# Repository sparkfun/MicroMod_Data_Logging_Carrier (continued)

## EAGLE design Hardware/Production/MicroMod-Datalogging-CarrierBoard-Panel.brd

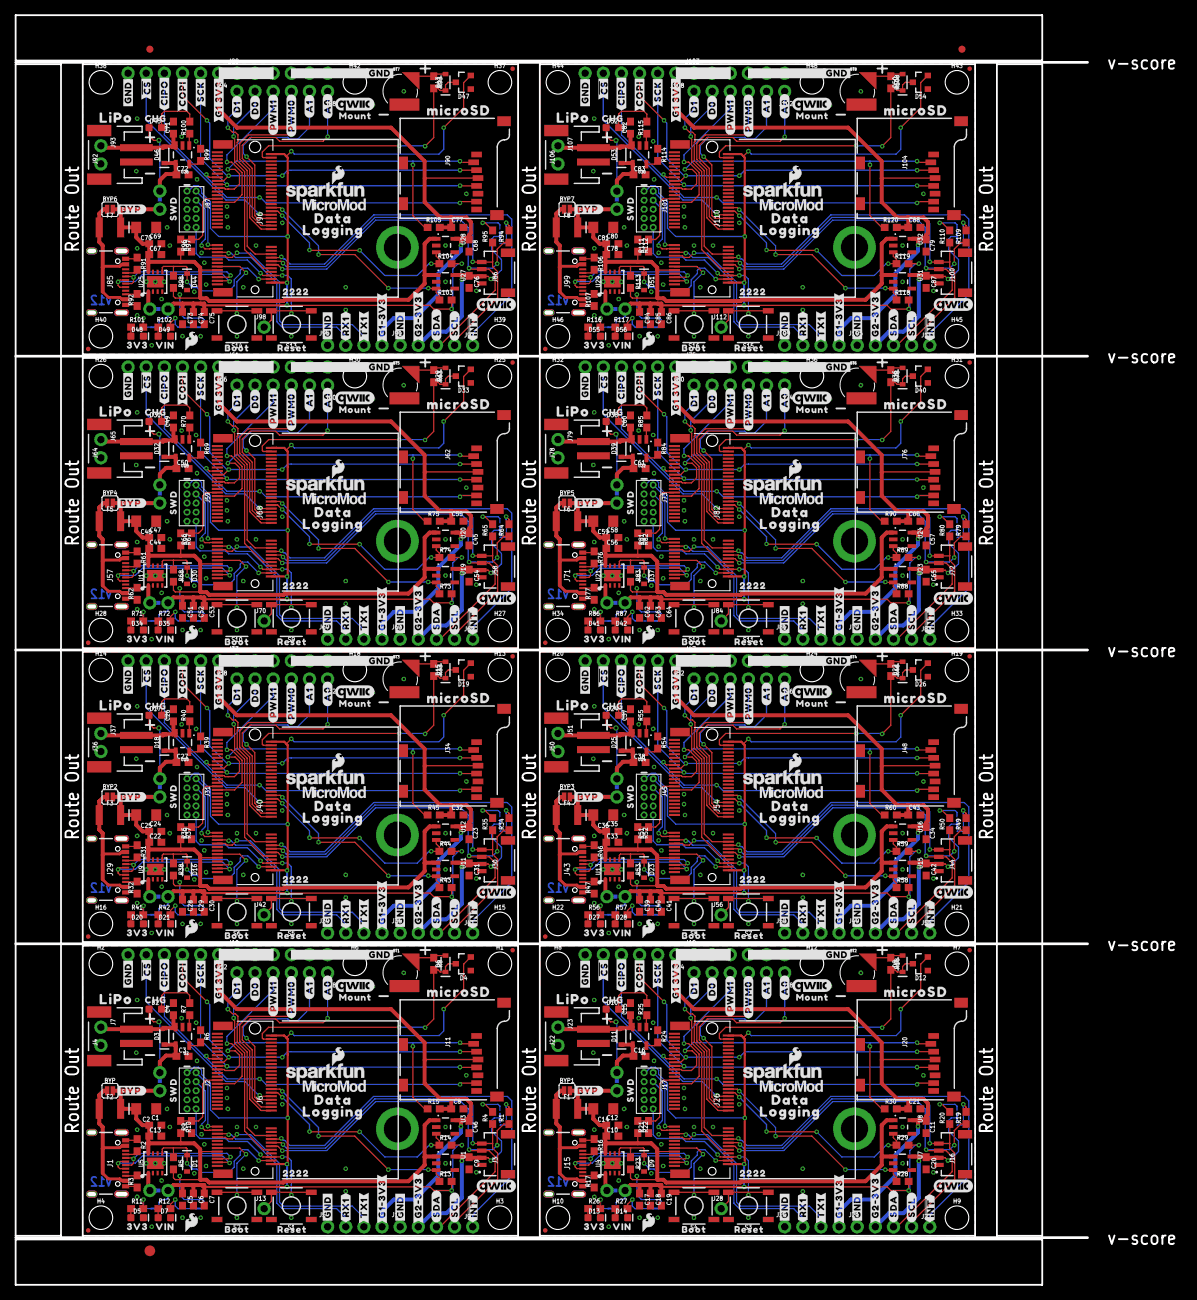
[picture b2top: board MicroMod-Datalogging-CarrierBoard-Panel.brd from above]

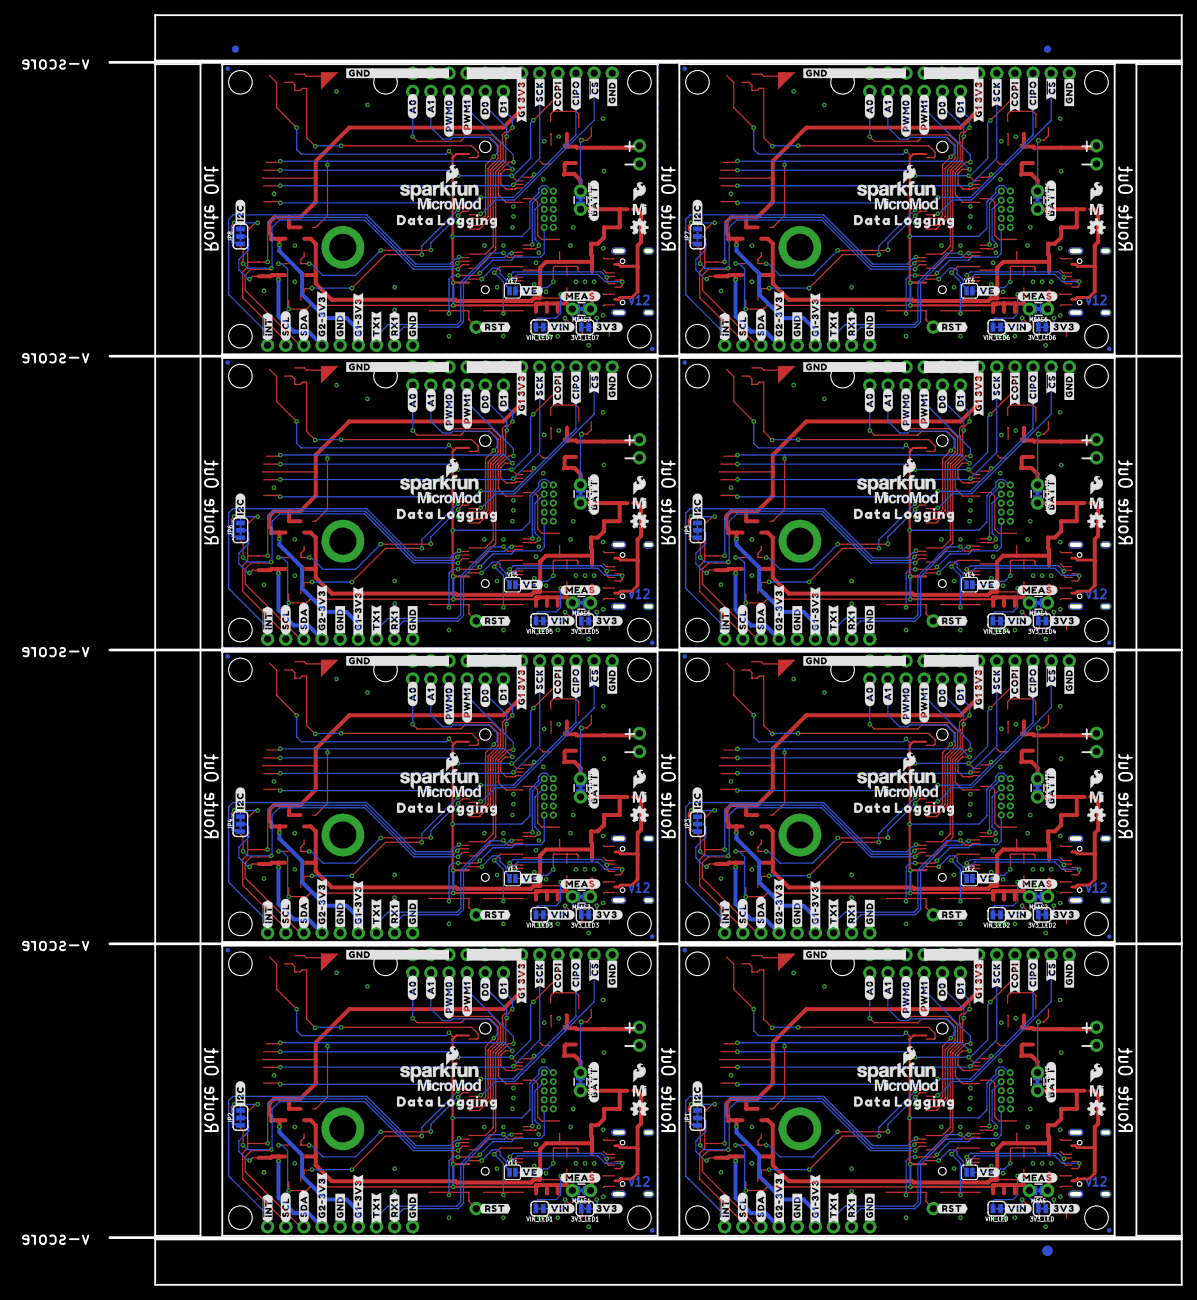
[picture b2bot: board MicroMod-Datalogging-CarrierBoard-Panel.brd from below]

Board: 2 copper layers, 163.1 x 177.5 mm, 1190 parts (355 on the bottom side), 392 nets.

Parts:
3V3_LED, 3V3_LED1, 3V3_LED2, 3V3_LED3, 3V3_LED4, 3V3_LED5, 3V3_LED6, 3V3_LED7: SMT-JUMPER_2_NC_TRACE_SILK
BT1, BT2, BT3, BT4, BT5, BT6, BT7, BT8: ML414H; ML414H_IV01E
BYP, BYP1, BYP2, BYP3, BYP4, BYP5, BYP6, BYP7: JUMPER-SMT_2_NO_SILK; SMT-JUMPER_2_NO_SILK
C1, C6, C11, C12, C18, C23, C24, C29, C34, C35, C40, C45, C46, C47, C52, C57, C58, C63, C68, C69, C74, C79, C80, C85: 0.1uF; 0603
C2, C14, C25, C36, C48, C59, C70, C81: 10uF; EIA3216
C3, C4, C15, C16, C26, C27, C37, C38, C49, C50, C60, C61, C71, C72, C82, C83: 4.7uF; 0603
C5, C8, C9, C17, C20, C21, C28, C31, C32, C39, C42, C43, C51, C54, C55, C62, C65, C66, C73, C76, C77, C84, C87, C88: 1.0uF; 0603
C7, C10, C13, C19, C22, C30, C33, C41, C44, C53, C56, C64, C67, C75, C78, C86: 0.22uF; 0603
D1, D9, D16, D23, D30, D37, D44, D51: 3.3V; SOD-323
D2, D7, D10, D14, D17, D21, D24, D28, D31, D35, D38, D42, D45, D49, D52, D56: Yellow; LED-0603
D3, D6, D8, D11, D15, D18, D22, D25, D29, D32, D36, D39, D43, D46, D50, D53: 3A/10V/280mV; SOD-323
D4, D12, D19, D26, D33, D40, D47, D54: BAS70-05; SOT23-3
D5, D13, D20, D27, D34, D41, D48, D55: RED; LED-0603
E$1, E$2, E$3, E$4: FIDUCIAL-1X2
E$5, E$6: FIDUCIAL-1.5X3
F1, F2, F3, F4, F5, F6, F7, F8: 6V/2A; 1210
FD1, FD2, FD3, FD4, FD5, FD6, FD7, FD8, FD9, FD10, FD11, FD12, FD13, FD14, FD15, FD16, FD17, FD18, FD19, FD20, FD21, FD22, FD23, FD24, FD25, FD26, FD27, FD28, FD29, FD30, FD31, FD32: FIDUCIALUFIDUCIAL; FIDUCIAL-MICRO
H1, H2, H3, H4, H6, H7, H8, H9, H10, H12, H13, H14, H15, H16, H18, H19, H20, H21, H22, H24, H25, H26, H27, H28, H30, H31, H32, H33, H34, H36, H37, H38, H39, H40, H42, H43, H44, H45, H46, H48: STAND-OFF
H5, H11, H17, H23, H29, H35, H41, H47: STAND-OFF-REFLOW2.5MM_TALL; STAND-OFF-REFLOW-M2.5
J1, J15, J29, J43, J57, J71, J85, J99: USB-C-16P-2LAYER-PADS
J2, J17, J31, J45, J59, J73, J87, J101: JTAG; 2X5-PTH-1.27MM
J3, J16, J30, J44, J58, J72, J86, J100: QWIIC_RIGHT_ANGLE; JST04_1MM_RA
J4, J22, J36, J50, J64, J78, J92, J106: JST-2-SMD
J5, J25, J39, J53, J67, J81, J95, J109: UART; 1X04_NO_SILK
J6, J26, J40, J54, J68, J82, J96, J110: MICROMOD-2222-C; M.2-CONNECTOR-E
J7, J23, J37, J51, J65, J79, J93, J107: 1X02_NO_SILK
J8, J18, J32, J46, J60, J74, J88, J102: Dedicated; 1X06_NO_SILK
J9, J13, J27, J28, J41, J42, J55, J56, J69, J70, J83, J84, J97, J98, J111, J112: 1X01_NO_SILK
J10, J19, J33, J47, J61, J75, J89, J103: 1X06_NO_SILK
J11, J20, J34, J48, J62, J76, J90, J104: microSD; MICRO-SD-SOCKET
J12, J24, J38, J52, J66, J80, J94, J108: SPI; 1X06_NO_SILK
J14, J21, J35, J49, J63, J77, J91, J105: I2C; 1X04_NO_SILK
JP1, JP2, JP3, JP4, JP5, JP6, JP7, JP8: SMT-JUMPER_3_2-NC_TRACE_SILK
LOGO1, LOGO4, LOGO6, LOGO9, LOGO11, LOGO14, LOGO16, LOGO19, LOGO21, LOGO24, LOGO26, LOGO29, LOGO31, LOGO34, LOGO36, LOGO39: SFE_LOGO_NAME_FLAME.1_INCH; SFE_LOGO_NAME_FLAME_.1
LOGO2, LOGO5, LOGO7, LOGO10, LOGO12, LOGO15, LOGO17, LOGO20, LOGO22, LOGO25, LOGO27, LOGO30, LOGO32, LOGO35, LOGO37, LOGO40: QWIIC_LOGO_CONNECTOR; QWIIC_5.5MM
LOGO3, LOGO8, LOGO13, LOGO18, LOGO23, LOGO28, LOGO33, LOGO38: OSHW-LOGOMINI; OSHW-LOGO-MINI
MEAS, MEAS1, MEAS2, MEAS3, MEAS4, MEAS5, MEAS6, MEAS7: COMBO-JUMPER_2_NC_TRACE
MEAS_BATT, MEAS_BATT1, MEAS_BATT2, MEAS_BATT3, MEAS_BATT4, MEAS_BATT5, MEAS_BATT6, MEAS_BATT7: COMBO-JUMPER_2_NC_TRACE
R1, R4, R6, R19, R20, R24, R34, R35, R39, R49, R50, R54, R64, R65, R69, R79, R80, R84, R94, R95, R99, R109, R110, R114: 2.2k; 0603
R2, R3, R16, R17, R31, R32, R46, R47, R61, R62, R76, R77, R91, R92, R106, R107: 5.1k; 0603
R5, R13, R14, R15, R23, R28, R29, R30, R38, R43, R44, R45, R53, R58, R59, R60, R68, R73, R74, R75, R83, R88, R89, R90, R98, R103, R104, R105, R113, R118, R119, R120: 100k; 0603
R7, R11, R25, R26, R40, R41, R55, R56, R70, R71, R85, R86, R100, R101, R115, R116: 1k; 0603
R8, R18, R33, R48, R63, R78, R93, R108: 3.3k; 0603
R9, R21, R36, R51, R66, R81, R96, R111: 10k; 0603
R10, R22, R37, R52, R67, R82, R97, R112: 20k; 0603
R12, R27, R42, R57, R72, R87, R102, R117: 4.7k; 0603
S1, S3, S5, S7, S9, S11, S13, S15: Reset; TACTILE_SWITCH_SMD_5.2MM
S2, S4, S6, S8, S10, S12, S14, S16: BOOT; TACTILE_SWITCH_SMD_5.2MM
U1, U3, U7, U8, U11, U12, U15, U16, U19, U20, U23, U24, U27, U28, U31, U32: 3.3V; SOT23-5
U2, U6, U10, U14, U18, U22, U26, U30: MCP73831; SOT23-5
U4, U5, U9, U13, U17, U21, U25, U29: AP7361C-33; UDFN-8
U$1, U$45, U$47, U$66, U$145, U$147, U$216, U$218, U$287, U$289, U$358, U$360, U$429, U$431, U$500, U$502: SFE_LOGO_FLAME_.1
U$2, U$58, U$76, U$118, U$156, U$189, U$227, U$260, U$298, U$331, U$369, U$402, U$440, U$473, U$511, U$544: #D1#0
U$3, U$59, U$77, U$119, U$157, U$190, U$228, U$261, U$299, U$332, U$370, U$403, U$441, U$474, U$512, U$545: #D0#0
U$4, U$133, U$204, U$275, U$346, U$417, U$488, U$559: #3V3#2
U$5, U$137, U$208, U$279, U$350, U$421, U$492, U$563: #BATT#0
U$6, U$18, U$24, U$27, U$32, U$34, U$36, U$42, U$105, U$106, U$107, U$108, U$109, U$110, U$138, U$142, U$176, U$177, U$178, U$179, U$180, U$181, U$209, U$213, U$247, U$248, U$249, U$250, U$251, U$252, U$280, U$284, U$318, U$319, U$320, U$321, U$322, U$323, U$351, U$355, U$389, U$390, U$391, U$392, U$393, U$394, U$422, U$426, U$460, U$461, U$462, U$463, U$464, U$465, U$493, U$497, U$531, U$532, U$533, U$534, U$535, U$536, U$564, U$568: #GND#0
U$7, U$8, U$52, U$53, U$150, U$151, U$221, U$222, U$292, U$293, U$363, U$364, U$434, U$435, U$505, U$506: #SCK#0
U$9, U$68, U$81, U$120, U$161, U$191, U$232, U$262, U$303, U$333, U$374, U$404, U$445, U$475, U$516, U$546: #PWM1#1
U$10, U$67, U$80, U$121, U$160, U$192, U$231, U$263, U$302, U$334, U$373, U$405, U$444, U$476, U$515, U$547: #PWM0#0
U$11, U$125, U$196, U$267, U$338, U$409, U$480, U$551: MICROSD0
U$12, U$61, U$79, U$122, U$159, U$193, U$230, U$264, U$301, U$335, U$372, U$406, U$443, U$477, U$514, U$548: #A1#2
U$13, U$60, U$78, U$123, U$158, U$194, U$229, U$265, U$300, U$336, U$371, U$407, U$442, U$478, U$513, U$549: #A0#3
U$14, U$124, U$195, U$266, U$337, U$408, U$479, U$550: MOUNT0
U$15, U$126, U$197, U$268, U$339, U$410, U$481, U$552: LIPO0
U$16, U$23, U$127, U$130, U$198, U$201, U$269, U$272, U$340, U$343, U$411, U$414, U$482, U$485, U$553, U$556: DATA0
U$17, U$71, U$86, U$111, U$164, U$182, U$235, U$253, U$306, U$324, U$377, U$395, U$448, U$466, U$519, U$537: #RX1#1
U$19, U$26, U$128, U$131, U$199, U$202, U$270, U$273, U$341, U$344, U$412, U$415, U$483, U$486, U$554, U$557: LOGGING1
U$20, U$129, U$200, U$271, U$342, U$413, U$484, U$555: 22220
U$21, U$84, U$89, U$112, U$167, U$183, U$238, U$254, U$309, U$325, U$380, U$396, U$451, U$467, U$522, U$538: #TX1#2
U$22, U$132, U$203, U$274, U$345, U$416, U$487, U$558: #I2C#0
U$25, U$85, U$90, U$113, U$168, U$184, U$239, U$255, U$310, U$326, U$381, U$397, U$452, U$468, U$523, U$539: #G1#3V3#0
U$28, U$134, U$205, U$276, U$347, U$418, U$489, U$560: #MEAS#3
U$29, U$70, U$83, U$114, U$163, U$185, U$234, U$256, U$305, U$327, U$376, U$398, U$447, U$469, U$518, U$540: #G2#3V3#3
U$30, U$135, U$206, U$277, U$348, U$419, U$490, U$561: #RST#0
U$31, U$75, U$88, U$115, U$166, U$186, U$237, U$257, U$308, U$328, U$379, U$399, U$450, U$470, U$521, U$541: #SDA#4
U$33, U$136, U$207, U$278, U$349, U$420, U$491, U$562: #VIN#1
U$35, U$74, U$87, U$116, U$165, U$187, U$236, U$258, U$307, U$329, U$378, U$400, U$449, U$471, U$520, U$542: #SCL#5
U$37, U$44, U$46, U$63, U$144, U$146, U$215, U$217, U$286, U$288, U$357, U$359, U$428, U$430, U$499, U$501: MICROMOD_LOGO_.35
U$38, U$69, U$82, U$117, U$162, U$188, U$233, U$259, U$304, U$330, U$375, U$401, U$446, U$472, U$517, U$543: ##INT##6
U$39, U$40, U$139, U$140, U$210, U$211, U$281, U$282, U$352, U$353, U$423, U$424, U$494, U$495, U$565, U$566: #CIPO#0
U$41, U$141, U$212, U$283, U$354, U$425, U$496, U$567: #VE#0
U$43, U$62, U$143, U$214, U$285, U$356, U$427, U$498: MICROMOD_MI_LOGO_.35
U$48, U$49, U$72, U$73, U$148, U$149, U$219, U$220, U$290, U$291, U$361, U$362, U$432, U$433, U$503, U$504: #COPI#0
U$50, U$51, U$54, U$55, U$152, U$153, U$223, U$224, U$294, U$295, U$365, U$366, U$436, U$437, U$507, U$508: ##CS##0
U$56, U$57, U$64, U$65, U$154, U$155, U$225, U$226, U$296, U$297, U$367, U$368, U$438, U$439, U$509, U$510: #G1_3V3#0
U$91, U$98, U$169, U$240, U$311, U$382, U$453, U$524: BOOT0
U$92, U$99, U$170, U$241, U$312, U$383, U$454, U$525: RESET1
U$93, U$100, U$171, U$242, U$313, U$384, U$455, U$526: 3V30
U$94, U$101, U$172, U$243, U$314, U$385, U$456, U$527: VIN1
U$95, U$102, U$173, U$244, U$315, U$386, U$457, U$528: #BYP#3
U$96, U$103, U$174, U$245, U$316, U$387, U$458, U$529: CHG1
U$97, U$104, U$175, U$246, U$317, U$388, U$459, U$530: SWD0
VE, VE1, VE2, VE3, VE4, VE5, VE6, VE7: SMT-JUMPER_2_NO_SILK
VIN_LED, VIN_LED1, VIN_LED2, VIN_LED3, VIN_LED4, VIN_LED5, VIN_LED6, VIN_LED7: SMT-JUMPER_2_NC_TRACE_SILK

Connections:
3.3V: 3V3_LED.2, C5.1, C6.1, C7.1, D4.2, J2.1, J6.2, J6.74, MEAS.2, MEAS.4, R13.2, R14.2
3.3V1: 3V3_LED1.2, C17.1, C18.1, C19.1, D12.2, J17.1, J26.2, J26.74, MEAS1.2, MEAS1.4, R28.2, R29.2
3.3V2: 3V3_LED2.2, C28.1, C29.1, C30.1, D19.2, J31.1, J40.2, J40.74, MEAS2.2, MEAS2.4, R43.2, R44.2
3.3V3: 3V3_LED3.2, C39.1, C40.1, C41.1, D26.2, J45.1, J54.2, J54.74, MEAS3.2, MEAS3.4, R58.2, R59.2
3.3V4: 3V3_LED4.2, C51.1, C52.1, C53.1, D33.2, J59.1, J68.2, J68.74, MEAS4.2, MEAS4.4, R73.2, R74.2
3.3V5: 3V3_LED5.2, C62.1, C63.1, C64.1, D40.2, J73.1, J82.2, J82.74, MEAS5.2, MEAS5.4, R88.2, R89.2
3.3V6: 3V3_LED6.2, C73.1, C74.1, C75.1, D47.2, J87.1, J96.2, J96.74, MEAS6.2, MEAS6.4, R103.2, R104.2
3.3V7: 3V3_LED7.2, C84.1, C85.1, C86.1, D54.2, J101.1, J110.2, J110.74, MEAS7.2, MEAS7.4, R118.2, R119.2
3.3V_EN: J6.4, VE.1
3.3V_EN1: J26.4, VE1.1
3.3V_EN2: J40.4, VE2.1
3.3V_EN3: J54.4, VE3.1
3.3V_EN4: J68.4, VE4.1
3.3V_EN5: J82.4, VE5.1
3.3V_EN6: J96.4, VE6.1
3.3V_EN7: J110.4, VE7.1
3.3V_EN_VE: D1.C, R5.1, U5.5, VE.2
3.3V_EN_VE1: D9.C, R23.1, U4.5, VE1.2
3.3V_EN_VE2: D16.C, R38.1, U9.5, VE2.2
3.3V_EN_VE3: D23.C, R53.1, U13.5, VE3.2
3.3V_EN_VE4: D30.C, R68.1, U17.5, VE4.2
3.3V_EN_VE5: D37.C, R83.1, U21.5, VE5.2
3.3V_EN_VE6: D44.C, R98.1, U25.5, VE6.2
3.3V_EN_VE7: D51.C, R113.1, U29.5, VE7.2
3.3V_LP: C8.1, C46.1, J5.4, J10.1, J10.2, J10.3, J11.VCC, J12.1, R15.2, U3.5
3.3V_LP1: C11.1, C21.1, J19.1, J19.2, J19.3, J20.VCC, J24.1, J25.4, R30.2, U8.5
3.3V_LP2: C23.1, C32.1, J33.1, J33.2, J33.3, J34.VCC, J38.1, J39.4, R45.2, U12.5
3.3V_LP3: C34.1, C43.1, J47.1, J47.2, J47.3, J48.VCC, J52.1, J53.4, R60.2, U16.5
3.3V_LP4: C45.1, C55.1, J61.1, J61.2, J61.3, J62.VCC, J66.1, J67.4, R75.2, U20.5
3.3V_LP5: C57.1, C66.1, J75.1, J75.2, J75.3, J76.VCC, J80.1, J81.4, R90.2, U24.5
3.3V_LP6: C68.1, C77.1, J89.1, J89.2, J89.3, J90.VCC, J94.1, J95.4, R105.2, U28.5
3.3V_LP7: C79.1, C88.1, J103.1, J103.2, J103.3, J104.VCC, J108.1, J109.4, R120.2, U32.5
5V: C3.1, D2.A, D3.C, MEAS_BATT.1, MEAS_BATT.3, U2.4
5V1: C16.1, D10.A, D11.C, MEAS_BATT1.1, MEAS_BATT1.3, U6.4
5V2: C27.1, D17.A, D18.C, MEAS_BATT2.1, MEAS_BATT2.3, U10.4
5V3: C38.1, D24.A, D25.C, MEAS_BATT3.1, MEAS_BATT3.3, U14.4
5V4: C50.1, D31.A, D32.C, MEAS_BATT4.1, MEAS_BATT4.3, U18.4
5V5: C61.1, D38.A, D39.C, MEAS_BATT5.1, MEAS_BATT5.3, U22.4
5V6: C72.1, D45.A, D46.C, MEAS_BATT6.1, MEAS_BATT6.3, U26.4
5V7: C83.1, D52.A, D53.C, MEAS_BATT7.1, MEAS_BATT7.3, U30.4
!BOOT!: J6.11, S2.3, S2.4
!BOOT!1: J26.11, S4.3, S4.4
!BOOT!2: J40.11, S6.3, S6.4
!BOOT!3: J54.11, S8.3, S8.4
!BOOT!4: J68.11, S10.3, S10.4
!BOOT!5: J82.11, S12.3, S12.4
!BOOT!6: J96.11, S14.3, S14.4
!BOOT!7: J110.11, S16.3, S16.4
!RESET!: J2.10, J6.6, J13.1, S1.3, S1.4
!RESET!1: J17.10, J26.6, J28.1, S3.3, S3.4
!RESET!2: J31.10, J40.6, J42.1, S5.3, S5.4
!RESET!3: J45.10, J54.6, J56.1, S7.3, S7.4
!RESET!4: J59.10, J68.6, J70.1, S9.3, S9.4
!RESET!5: J73.10, J82.6, J84.1, S11.3, S11.4
!RESET!6: J87.10, J96.6, J98.1, S13.3, S13.4
!RESET!7: J101.10, J110.6, J112.1, S15.3, S15.4
A0: J6.34, J8.1
A1: J6.38, J8.2
A2: J18.1, J26.34
A3: J18.2, J26.38
A4: J32.1, J40.34
A5: J32.2, J40.38
A6: J46.1, J54.34
A7: J46.2, J54.38
A8: J60.1, J68.34
A9: J60.2, J68.38
A10: J74.1, J82.34
A11: J74.2, J82.38
A12: J88.1, J96.34
A13: J88.2, J96.38
A14: J102.1, J110.34
A15: J102.2, J110.38
CHG_LED: R7.1, U2.1
CHG_LED1: R25.1, U6.1
CHG_LED2: R40.1, U10.1
CHG_LED3: R55.1, U14.1
CHG_LED4: R70.1, U18.1
CHG_LED5: R85.1, U22.1
CHG_LED6: R100.1, U26.1
CHG_LED7: R115.1, U30.1
D0: J6.10, J8.5
D1: J6.18, J8.6
D2: J18.5, J26.10
D3: J18.6, J26.18
D4: J32.5, J40.10
D5: J32.6, J40.18
D6: J46.5, J54.10
D7: J46.6, J54.18
D8: J60.5, J68.10
D9: J60.6, J68.18
D10: J74.5, J82.10
D11: J74.6, J82.18
D12: J88.5, J96.10
D13: J88.6, J96.18
D14: J102.5, J110.10
D15: J102.6, J110.18
GND: BT1.-, C1.2, C2.-, C3.2, C4.2, C5.2, C6.2, C7.2, C8.2, C9.2, C13.2, C46.2, D1.A, D5.C, D7.C, H5.1, J1.GND, J1.GND2, J2.3, J2.5, J2.9, J3.1, J4.1, J5.1, J6.1, J6.7, J6.33, J6.36, J6.39, J6.45, J6.75, J7.2, J10.4, J10.5, J10.6, J11.CD1, J11.GND, J11.GND1, J11.GND3, J12.6, J14.1, R2.1, R3.1, R6.1, R9.1, S1.1, S1.2, S2.1, S2.2, U1.2, U2.2, U3.2, U5.4, U5.EP
GND1: BT2.-, C10.2, C11.2, C12.2, C14.-, C15.2, C16.2, C17.2, C18.2, C19.2, C20.2, C21.2, D9.A, D13.C, D14.C, H11.1, J15.GND, J15.GND2, J16.1, J17.3, J17.5, J17.9, J19.4, J19.5, J19.6, J20.CD1, J20.GND, J20.GND1, J20.GND3, J21.1, J22.1, J23.2, J24.6, J25.1, J26.1, J26.7, J26.33, J26.36, J26.39, J26.45, J26.75, R16.1, R17.1, R21.1, R24.1, S3.1, S3.2, S4.1, S4.2, U4.4, U4.EP, U6.2, U7.2, U8.2
GND2: BT3.-, C22.2, C23.2, C24.2, C25.-, C26.2, C27.2, C28.2, C29.2, C30.2, C31.2, C32.2, D16.A, D20.C, D21.C, H17.1, J29.GND, J29.GND2, J30.1, J31.3, J31.5, J31.9, J33.4, J33.5, J33.6, J34.CD1, J34.GND, J34.GND1, J34.GND3, J35.1, J36.1, J37.2, J38.6, J39.1, J40.1, J40.7, J40.33, J40.36, J40.39, J40.45, J40.75, R31.1, R32.1, R36.1, R39.1, S5.1, S5.2, S6.1, S6.2, U9.4, U9.EP, U10.2, U11.2, U12.2
GND3: BT4.-, C33.2, C34.2, C35.2, C36.-, C37.2, C38.2, C39.2, C40.2, C41.2, C42.2, C43.2, D23.A, D27.C, D28.C, H23.1, J43.GND, J43.GND2, J44.1, J45.3, J45.5, J45.9, J47.4, J47.5, J47.6, J48.CD1, J48.GND, J48.GND1, J48.GND3, J49.1, J50.1, J51.2, J52.6, J53.1, J54.1, J54.7, J54.33, J54.36, J54.39, J54.45, J54.75, R46.1, R47.1, R51.1, R54.1, S7.1, S7.2, S8.1, S8.2, U13.4, U13.EP, U14.2, U15.2, U16.2
GND4: BT5.-, C44.2, C45.2, C47.2, C48.-, C49.2, C50.2, C51.2, C52.2, C53.2, C54.2, C55.2, D30.A, D34.C, D35.C, H29.1, J57.GND, J57.GND2, J58.1, J59.3, J59.5, J59.9, J61.4, J61.5, J61.6, J62.CD1, J62.GND, J62.GND1, J62.GND3, J63.1, J64.1, J65.2, J66.6, J67.1, J68.1, J68.7, J68.33, J68.36, J68.39, J68.45, J68.75, R61.1, R62.1, R66.1, R69.1, S9.1, S9.2, S10.1, S10.2, U17.4, U17.EP, U18.2, U19.2, U20.2
GND5: BT6.-, C56.2, C57.2, C58.2, C59.-, C60.2, C61.2, C62.2, C63.2, C64.2, C65.2, C66.2, D37.A, D41.C, D42.C, H35.1, J71.GND, J71.GND2, J72.1, J73.3, J73.5, J73.9, J75.4, J75.5, J75.6, J76.CD1, J76.GND, J76.GND1, J76.GND3, J77.1, J78.1, J79.2, J80.6, J81.1, J82.1, J82.7, J82.33, J82.36, J82.39, J82.45, J82.75, R76.1, R77.1, R81.1, R84.1, S11.1, S11.2, S12.1, S12.2, U21.4, U21.EP, U22.2, U23.2, U24.2
GND6: BT7.-, C67.2, C68.2, C69.2, C70.-, C71.2, C72.2, C73.2, C74.2, C75.2, C76.2, C77.2, D44.A, D48.C, D49.C, H41.1, J85.GND, J85.GND2, J86.1, J87.3, J87.5, J87.9, J89.4, J89.5, J89.6, J90.CD1, J90.GND, J90.GND1, J90.GND3, J91.1, J92.1, J93.2, J94.6, J95.1, J96.1, J96.7, J96.33, J96.36, J96.39, J96.45, J96.75, R91.1, R92.1, R96.1, R99.1, S13.1, S13.2, S14.1, S14.2, U25.4, U25.EP, U26.2, U27.2, U28.2
GND7: BT8.-, C78.2, C79.2, C80.2, C81.-, C82.2, C83.2, C84.2, C85.2, C86.2, C87.2, C88.2, D51.A, D55.C, D56.C, H47.1, J99.GND, J99.GND2, J100.1, J101.3, J101.5, J101.9, J103.4, J103.5, J103.6, J104.CD1, J104.GND, J104.GND1, J104.GND3, J105.1, J106.1, J107.2, J108.6, J109.1, J110.1, J110.7, J110.33, J110.36, J110.39, J110.45, J110.75, R106.1, R107.1, R111.1, R114.1, S15.1, S15.2, S16.1, S16.2, U29.4, U29.EP, U30.2, U31.2, U32.2
HEADER_!CS!: J6.40, J12.5
HEADER_!CS!1: J24.5, J26.40
HEADER_!CS!2: J38.5, J40.40
HEADER_!CS!3: J52.5, J54.40
HEADER_!CS!4: J66.5, J68.40
HEADER_!CS!5: J80.5, J82.40
HEADER_!CS!6: J94.5, J96.40
HEADER_!CS!7: J108.5, J110.40
I2C_!INT!: J6.16, J9.1
I2C_!INT!1: J26.16, J27.1
I2C_!INT!2: J40.16, J41.1
I2C_!INT!3: J54.16, J55.1
I2C_!INT!4: J68.16, J69.1
I2C_!INT!5: J82.16, J83.1
I2C_!INT!6: J96.16, J97.1
I2C_!INT!7: J110.16, J111.1
I2C_SCL: J3.4, J6.14, J14.4, R4.1
I2C_SCL1: J16.4, J21.4, J26.14, R20.1
I2C_SCL2: J30.4, J35.4, J40.14, R35.1
I2C_SCL3: J44.4, J49.4, J54.14, R50.1
I2C_SCL4: J58.4, J63.4, J68.14, R65.1
I2C_SCL5: J72.4, J77.4, J82.14, R80.1
I2C_SCL6: J86.4, J91.4, J96.14, R95.1
I2C_SCL7: J100.4, J105.4, J110.14, R110.1
I2C_SDA: J3.3, J6.12, J14.3, R1.1
I2C_SDA1: J16.3, J21.3, J26.12, R19.1
I2C_SDA2: J30.3, J35.3, J40.12, R34.1
I2C_SDA3: J44.3, J49.3, J54.12, R49.1
I2C_SDA4: J58.3, J63.3, J68.12, R64.1
I2C_SDA5: J72.3, J77.3, J82.12, R79.1
I2C_SDA6: J86.3, J91.3, J96.12, R94.1
I2C_SDA7: J100.3, J105.3, J110.12, R109.1
unnamed: MEAS.1, MEAS.3, U5.1
unnamed: JP1.3, R4.2
unnamed: JP1.1, R1.2
unnamed: D2.C, R7.2
unnamed: D5.A, R11.1
unnamed: 3V3_LED.1, R11.2
unnamed: R6.2, U2.5
unnamed: R12.2, VIN_LED.1
unnamed: D7.A, R12.1
unnamed: J1.A5, R2.2
unnamed: J1.B5, R3.2
unnamed: J15.A5, R16.2
unnamed: J15.B5, R17.2
unnamed: BT1.+, D6.A, R8.1
unnamed: BT2.+, D8.A, R18.1
unnamed: JP2.3, R20.2
unnamed: JP2.1, R19.2
unnamed: MEAS1.1, MEAS1.3, U4.1
unnamed: R24.2, U6.5
unnamed: D10.C, R25.2
unnamed: 3V3_LED1.1, R26.2
unnamed: D13.A, R26.1
unnamed: R27.2, VIN_LED1.1
unnamed: D14.A, R27.1
unnamed: J29.A5, R31.2
unnamed: J29.B5, R32.2
unnamed: BT3.+, D15.A, R33.1
unnamed: JP3.3, R35.2
unnamed: JP3.1, R34.2
unnamed: MEAS2.1, MEAS2.3, U9.1
unnamed: R39.2, U10.5
unnamed: D17.C, R40.2
unnamed: 3V3_LED2.1, R41.2
unnamed: D20.A, R41.1
unnamed: R42.2, VIN_LED2.1
unnamed: D21.A, R42.1
unnamed: J43.A5, R46.2
unnamed: J43.B5, R47.2
unnamed: BT4.+, D22.A, R48.1
unnamed: JP4.3, R50.2
unnamed: JP4.1, R49.2
unnamed: MEAS3.1, MEAS3.3, U13.1
unnamed: R54.2, U14.5
unnamed: D24.C, R55.2
unnamed: 3V3_LED3.1, R56.2
unnamed: D27.A, R56.1
unnamed: R57.2, VIN_LED3.1
unnamed: D28.A, R57.1
unnamed: J57.A5, R61.2
unnamed: J57.B5, R62.2
unnamed: BT5.+, D29.A, R63.1
unnamed: JP5.3, R65.2
unnamed: JP5.1, R64.2
unnamed: MEAS4.1, MEAS4.3, U17.1
unnamed: R69.2, U18.5
unnamed: D31.C, R70.2
unnamed: 3V3_LED4.1, R71.2
unnamed: D34.A, R71.1
unnamed: R72.2, VIN_LED4.1
unnamed: D35.A, R72.1
unnamed: J71.A5, R76.2
unnamed: J71.B5, R77.2
unnamed: BT6.+, D36.A, R78.1
unnamed: JP6.3, R80.2
unnamed: JP6.1, R79.2
unnamed: MEAS5.1, MEAS5.3, U21.1
unnamed: R84.2, U22.5
unnamed: D38.C, R85.2
unnamed: 3V3_LED5.1, R86.2
unnamed: D41.A, R86.1
unnamed: R87.2, VIN_LED5.1
unnamed: D42.A, R87.1
unnamed: J85.A5, R91.2
unnamed: J85.B5, R92.2
unnamed: BT7.+, D43.A, R93.1
unnamed: JP7.3, R95.2
unnamed: JP7.1, R94.2
unnamed: MEAS6.1, MEAS6.3, U25.1
unnamed: R99.2, U26.5
unnamed: D45.C, R100.2
unnamed: 3V3_LED6.1, R101.2
unnamed: D48.A, R101.1
unnamed: R102.2, VIN_LED6.1
unnamed: D49.A, R102.1
unnamed: J99.A5, R106.2
unnamed: J99.B5, R107.2
unnamed: BT8.+, D50.A, R108.1
unnamed: JP8.3, R110.2
unnamed: JP8.1, R109.2
unnamed: MEAS7.1, MEAS7.3, U29.1
unnamed: R114.2, U30.5
unnamed: D52.C, R115.2
unnamed: 3V3_LED7.1, R116.2
unnamed: D55.A, R116.1
unnamed: R117.2, VIN_LED7.1
unnamed: D56.A, R117.1
PERIPHERAL_PWR_CTRL: J6.42, R14.1, U3.3
PERIPHERAL_PWR_CTRL1: J26.42, R29.1, U8.3
PERIPHERAL_PWR_CTRL2: J40.42, R44.1, U12.3
PERIPHERAL_PWR_CTRL3: J54.42, R59.1, U16.3
PERIPHERAL_PWR_CTRL4: J68.42, R74.1, U20.3
PERIPHERAL_PWR_CTRL5: J82.42, R89.1, U24.3
PERIPHERAL_PWR_CTRL6: J96.42, R104.1, U28.3
PERIPHERAL_PWR_CTRL7: J110.42, R119.1, U32.3
PWM0: J6.32, J8.3
PWM1: J6.47, J8.4
PWM2: J18.3, J26.32
PWM3: J18.4, J26.47
PWM4: J32.3, J40.32
PWM5: J32.4, J40.47
PWM6: J46.3, J54.32
PWM7: J46.4, J54.47
PWM8: J60.3, J68.32
PWM9: J60.4, J68.47
PWM10: J74.3, J82.32
PWM11: J74.4, J82.47
PWM12: J88.3, J96.32
PWM13: J88.4, J96.47
PWM14: J102.3, J110.32
PWM15: J102.4, J110.47
QWIIC_PWR: C9.1, J3.2, J14.2, JP1.2, U1.5
QWIIC_PWR1: C20.1, J16.2, J21.2, JP2.2, U7.5
QWIIC_PWR2: C31.1, J30.2, J35.2, JP3.2, U11.5
QWIIC_PWR3: C42.1, J44.2, J49.2, JP4.2, U15.5
QWIIC_PWR4: C54.1, J58.2, J63.2, JP5.2, U19.5
QWIIC_PWR5: C65.1, J72.2, J77.2, JP6.2, U23.5
QWIIC_PWR6: C76.1, J86.2, J91.2, JP7.2, U27.5
QWIIC_PWR7: C87.1, J100.2, J105.2, JP8.2, U31.5
QWIIC_PWR_CTRL: J6.44, R13.1, U1.3
QWIIC_PWR_CTRL1: J26.44, R28.1, U7.3
QWIIC_PWR_CTRL2: J40.44, R43.1, U11.3
QWIIC_PWR_CTRL3: J54.44, R58.1, U15.3
QWIIC_PWR_CTRL4: J68.44, R73.1, U19.3
QWIIC_PWR_CTRL5: J82.44, R88.1, U23.3
QWIIC_PWR_CTRL6: J96.44, R103.1, U27.3
QWIIC_PWR_CTRL7: J110.44, R118.1, U31.3
RTC_3V: D4.3, D6.C, J6.72, R8.2
RTC_3V1: D8.C, D12.3, J26.72, R18.2
RTC_3V2: D15.C, D19.3, J40.72, R33.2
RTC_3V3: D22.C, D26.3, J54.72, R48.2
RTC_3V4: D29.C, D33.3, J68.72, R63.2
RTC_3V5: D36.C, D40.3, J82.72, R78.2
RTC_3V6: D43.C, D47.3, J96.72, R93.2
RTC_3V7: D50.C, D54.3, J110.72, R108.2
RX1: J5.2, J6.19
RX2: J25.2, J26.19
RX3: J39.2, J40.19
RX4: J53.2, J54.19
RX5: J67.2, J68.19
RX6: J81.2, J82.19
RX7: J95.2, J96.19
RX8: J109.2, J110.19
SD_!CS!: J6.55, J11.CS/DAT3, R15.1
SD_!CS!1: J20.CS/DAT3, J26.55, R30.1
SD_!CS!2: J34.CS/DAT3, J40.55, R45.1
SD_!CS!3: J48.CS/DAT3, J54.55, R60.1
SD_!CS!4: J62.CS/DAT3, J68.55, R75.1
SD_!CS!5: J76.CS/DAT3, J82.55, R90.1
SD_!CS!6: J90.CS/DAT3, J96.55, R105.1
SD_!CS!7: J104.CS/DAT3, J110.55, R120.1
SPI_CIPO: J6.61, J11.DO/DAT0, J12.4
SPI_CIPO1: J20.DO/DAT0, J24.4, J26.61
SPI_CIPO2: J34.DO/DAT0, J38.4, J40.61
SPI_CIPO3: J48.DO/DAT0, J52.4, J54.61
SPI_CIPO4: J62.DO/DAT0, J66.4, J68.61
SPI_CIPO5: J76.DO/DAT0, J80.4, J82.61
SPI_CIPO6: J90.DO/DAT0, J94.4, J96.61
SPI_CIPO7: J104.DO/DAT0, J108.4, J110.61
SPI_COPI: J6.59, J11.DI/CMD, J12.3
SPI_COPI1: J20.DI/CMD, J24.3, J26.59
SPI_COPI2: J34.DI/CMD, J38.3, J40.59
SPI_COPI3: J48.DI/CMD, J52.3, J54.59
SPI_COPI4: J62.DI/CMD, J66.3, J68.59
SPI_COPI5: J76.DI/CMD, J80.3, J82.59
SPI_COPI6: J90.DI/CMD, J94.3, J96.59
SPI_COPI7: J104.DI/CMD, J108.3, J110.59
SPI_SCK: J6.57, J11.SCLK, J12.2
SPI_SCK1: J20.SCLK, J24.2, J26.57
SPI_SCK2: J34.SCLK, J38.2, J40.57
SPI_SCK3: J48.SCLK, J52.2, J54.57
SPI_SCK4: J62.SCLK, J66.2, J68.57
SPI_SCK5: J76.SCLK, J80.2, J82.57
SPI_SCK6: J90.SCLK, J94.2, J96.57
SPI_SCK7: J104.SCLK, J108.2, J110.57
SWDCK: J2.4, J6.21
SWDCK1: J17.4, J26.21
SWDCK2: J31.4, J40.21
SWDCK3: J45.4, J54.21
SWDCK4: J59.4, J68.21
SWDCK5: J73.4, J82.21
SWDCK6: J87.4, J96.21
SWDCK7: J101.4, J110.21
SWDIO: J2.2, J6.23
SWDIO1: J17.2, J26.23
SWDIO2: J31.2, J40.23
SWDIO3: J45.2, J54.23
SWDIO4: J59.2, J68.23
SWDIO5: J73.2, J82.23
SWDIO6: J87.2, J96.23
SWDIO7: J101.2, J110.23
TX1: J5.3, J6.17
TX2: J25.3, J26.17
TX3: J39.3, J40.17
TX4: J53.3, J54.17
TX5: J67.3, J68.17
TX6: J81.3, J82.17
TX7: J95.3, J96.17
TX8: J109.3, J110.17
USB_D+: J1.A6, J1.B6, J6.3
USB_D+1: J15.A6, J15.B6, J26.3
USB_D+2: J29.A6, J29.B6, J40.3
USB_D+3: J43.A6, J43.B6, J54.3
USB_D+4: J57.A6, J57.B6, J68.3
USB_D+5: J71.A6, J71.B6, J82.3
USB_D+6: J85.A6, J85.B6, J96.3
USB_D+7: J99.A6, J99.B6, J110.3
USB_D-: J1.A7, J1.B7, J6.5
USB_D-1: J15.A7, J15.B7, J26.5
USB_D-2: J29.A7, J29.B7, J40.5
USB_D-3: J43.A7, J43.B7, J54.5
USB_D-4: J57.A7, J57.B7, J68.5
USB_D-5: J71.A7, J71.B7, J82.5
USB_D-6: J85.A7, J85.B7, J96.5
USB_D-7: J99.A7, J99.B7, J110.5
VIN: BYP.2, C1.1, C2.+, C13.1, F2.2, J6.9, MEAS_BATT.2, MEAS_BATT.4, R5.2, R10.2, U1.1, U3.1, U5.8, VIN_LED.2
VIN1: BYP1.2, C10.1, C12.1, C14.+, F1.2, J26.9, MEAS_BATT1.2, MEAS_BATT1.4, R22.2, R23.2, U4.8, U7.1, U8.1, VIN_LED1.2
VIN2: BYP2.2, C22.1, C24.1, C25.+, F3.2, J40.9, MEAS_BATT2.2, MEAS_BATT2.4, R37.2, R38.2, U9.8, U11.1, U12.1, VIN_LED2.2
VIN3: BYP3.2, C33.1, C35.1, C36.+, F4.2, J54.9, MEAS_BATT3.2, MEAS_BATT3.4, R52.2, R53.2, U13.8, U15.1, U16.1, VIN_LED3.2
VIN4: BYP4.2, C44.1, C47.1, C48.+, F5.2, J68.9, MEAS_BATT4.2, MEAS_BATT4.4, R67.2, R68.2, U17.8, U19.1, U20.1, VIN_LED4.2
VIN5: BYP5.2, C56.1, C58.1, C59.+, F6.2, J82.9, MEAS_BATT5.2, MEAS_BATT5.4, R82.2, R83.2, U21.8, U23.1, U24.1, VIN_LED5.2
VIN6: BYP6.2, C67.1, C69.1, C70.+, F7.2, J96.9, MEAS_BATT6.2, MEAS_BATT6.4, R97.2, R98.2, U25.8, U27.1, U28.1, VIN_LED6.2
VIN7: BYP7.2, C78.1, C80.1, C81.+, F8.2, J110.9, MEAS_BATT7.2, MEAS_BATT7.4, R112.2, R113.2, U29.8, U31.1, U32.1, VIN_LED7.2
VIN/1: J26.49, R21.2, R22.1
VIN/2: J40.49, R36.2, R37.1
VIN/3: J6.49, R9.2, R10.1
VIN/4: J54.49, R51.2, R52.1
VIN/5: J68.49, R66.2, R67.1
VIN/6: J82.49, R81.2, R82.1
VIN/7: J96.49, R96.2, R97.1
VIN/8: J110.49, R111.2, R112.1
V_BATT: C4.1, D3.A, J4.2, J7.1, U2.3
V_BATT1: C15.1, D11.A, J22.2, J23.1, U6.3
V_BATT2: C26.1, D18.A, J36.2, J37.1, U10.3
V_BATT3: C37.1, D25.A, J50.2, J51.1, U14.3
V_BATT4: C49.1, D32.A, J64.2, J65.1, U18.3
V_BATT5: C60.1, D39.A, J78.2, J79.1, U22.3
V_BATT6: C71.1, D46.A, J92.2, J93.1, U26.3
V_BATT7: C82.1, D53.A, J106.2, J107.1, U30.3
V_USB: BYP.1, F2.1, J1.VBUS1, J1.VBUS2
V_USB1: BYP1.1, F1.1, J15.VBUS1, J15.VBUS2
V_USB2: BYP2.1, F3.1, J29.VBUS1, J29.VBUS2
V_USB3: BYP3.1, F4.1, J43.VBUS1, J43.VBUS2
V_USB4: BYP4.1, F5.1, J57.VBUS1, J57.VBUS2
V_USB5: BYP5.1, F6.1, J71.VBUS1, J71.VBUS2
V_USB6: BYP6.1, F7.1, J85.VBUS1, J85.VBUS2
V_USB7: BYP7.1, F8.1, J99.VBUS1, J99.VBUS2

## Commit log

2020-05-05 File cleanup
2020-05-05 Update v-reg device
2020-08-14 Change peripheral power to regulators. Upgrade buzzard labels. Add VE jumper.
2020-09-10 Update MicroMod connector with new SPI port assignments.
2020-10-19 Create README
    Initial commit for README
2020-10-29 Swap logic of power control functions
2020-10-29 Fix image URL
2020-11-20 Create License.md
    Added license
2021-11-05 Change SD to pure SPI connection.
